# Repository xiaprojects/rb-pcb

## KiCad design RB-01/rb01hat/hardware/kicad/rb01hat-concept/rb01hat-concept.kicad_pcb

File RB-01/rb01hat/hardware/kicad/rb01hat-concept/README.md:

# RB01HAT Rev A concept board

**This is a visualisation, not the Rev A design. Do not fabricate it.** It shows what the plan in
[docs/06-custom-pcb.md](../../../docs/06-custom-pcb.md) could look like. The Rev 0 bring-up gate in
[hardware/kicad/README.md](../README.md) still applies, and `hardware/*.csv` stays the source of truth.

Everything here is generated. Change `generate.py`, not the KiCad files.

## What it is

- HAT+ outline, 65 x 56.5 mm, four layers: F.Cu signals, In1 GND, In2 3V3, B.Cu signals.
- Parts sit in zones Z1-Z6 of [docs/03-mechanical.md](../../../docs/03-mechanical.md).
- Nets and refdes come from [hardware/netlist.csv](../../netlist.csv). The script stops if any on-board row
  doesn't land on a pad of that net. U9-U12 and J12 are not here: they belong to the extension.
- Fully routed, and the KiCad DRC passes with 0 errors, 0 warnings and 0 unconnected items.
- Chip pinouts were read from the vendor datasheets (listed at `PIN_MAP` in `generate.py`).

A clean DRC proves the copper is consistent with the rules. It doesn't prove the circuit works.

## Renders

In `renders/`, 3840 x 2160 JPG: `-hero` and `-right` (3/4 views), `-top`, `-bottom`.

## Regenerate

```bash
python3 generate.py            # board, routing, DRC
python3 generate.py --preview  # plus 1600 x 900 renders
python3 generate.py --render   # plus 4K renders (several minutes)
```

It needs the system Python with KiCad 9's `pcbnew`, numpy and Pillow, plus a C compiler for `astar.c`. The
`kicad-packages3d` package is not installed here, so the first run downloads the 3D models it needs into
`3dmodels/`.

## Defaults for the open decisions

These are placeholders so a board could be drawn. They are not decisions.

| ID | Used here | Why |
|---|---|---|
| RA-1 IMU | ICM-20948 with 1.8 V LDO and I2C translator | The netlist part. Lifecycle status not checked. |
| RA-2 Outline | A: HAT+ outline, EGT bank off-board on J11 | Doc 06 recommendation |
| RA-3 TC connectors | 3.5 mm 2-pole terminal blocks, wires leaving over the top edge | Keeps leads off the board; other edges are taken by the extension and J2 |
| RA-4 Power | Pi 3V3, as in the netlist | Fewest added parts. Doc 06 prefers a local LDO. |
| RA-5 BME680 | On-board peninsula with milled slots and no copper pour | Doc 06 |
| RA-6 HAT+ ID pins | RB-EMS mapping unchanged (I2C0 on GPIO0/1) | Matches the netlist; keeps the HAT+ deviation |
| RA-7 Off-HAT signals | No connectors | Not in the netlist |

## Added parts (not in netlist.csv)

The DIY modules carry these on board; a chip-down board has to supply them.

| Refdes | Purpose |
|---|---|
| U15, R14-R16, C21 | PCA9306 between 3V3 I2C1 and the IMU's 1.8 V I/O, EN network, 1.8 V pull-ups |
| U16, C19, C20 | AP2112K-1.8 LDO for the IMU |
| C16-C18 | IMU VDD, VDDIO and REGOUT capacitors |
| J3-J6 | CHT1-CHT4 terminal blocks |
| C4-C15 | MAX31856 AVDD, DVDD and T+/T- capacitors |
| C22-C25, R17-R19 | BME680, ADS1115 and U14 decoupling, 5 V pull-ups, U14 EN network |
| R20-R23, C26-C29 | ADC input RC filters |

U13, R13 and TP1 are DNP on the DIY build but fitted here, because HAT+ needs the ID EEPROM.

## Not done

A real Rev A needs at least these:

- **A schematic and ERC.** There is no schematic: the board comes straight from the CSV and the tables in `generate.py`.
- **FFC access.** The HAT+ examples have a PCIe FFC cut-out in the left edge (y 20-37) and a display FFC slot.
  RB-01 uses both PCIe and DSI. This board has neither, and the BME680 peninsula sits in that left-edge band.
- **Second ADS1115 at 0x49.** rb-ems-go now reads `oilpressure` there, so A3 is out of date. See below.
- **Doc 06 circuitry left out:** 33 Ohm series resistors on SCLK and MOSI, clamps and the battery divider on the
  ADC inputs, ferrite-split supplies.
- **Thermocouple layout.** No isothermal copper islands, and T+/T- are not routed as tight pairs.
- **Layout review.** `generate.py` holds a simple maze router: no length or impedance control, and nobody has
  reviewed the routing, the return paths or the assembly.
- **Footprint checks.** `MS4525DO_DS_DIP-8` is drawn from the datasheet outline; confirm pads and drills against
  TE's current drawing. U1 uses a generic 3 x 3 mm QFN-24 with the exposed pad removed, because the ICM-20948 die
  pad must not be soldered; confirm it against the TDK land pattern.

## Known differences from the docs

- **Header position.** [docs/03-mechanical.md](../../../docs/03-mechanical.md) puts the 40-pin header at x = 29 from
  the board corner. The Pi 5 drawing and the HAT+ examples measure that 29 from the hole, so the centre is at
  x = 32.5 and pin 1 at x = 8.37. This board uses the drawing.
- **ADC channels.** Since rb-ems-go `55f0627` (2026-10-10), `ems-adc.json` reads A2-A3 as a differential pair and
  `oilpressure` at address 0x49. J2 and U8 follow `netlist.csv`, which still has oil pressure on A3.

## Render notes

- The MS4525DO 3D model is a simple one made by `generate.py` from the datasheet outline.
- U8 shows KiCad's MSOP-10 model, because the library has no VSSOP-10 model. The outline is the same.
- Straight-down views use side lights only, because a light on the vertical axis mirrors off the mask and turns it
  pink. Their cast shadows are off, through a throwaway `KICAD_CONFIG_HOME`; your own KiCad settings aren't touched.

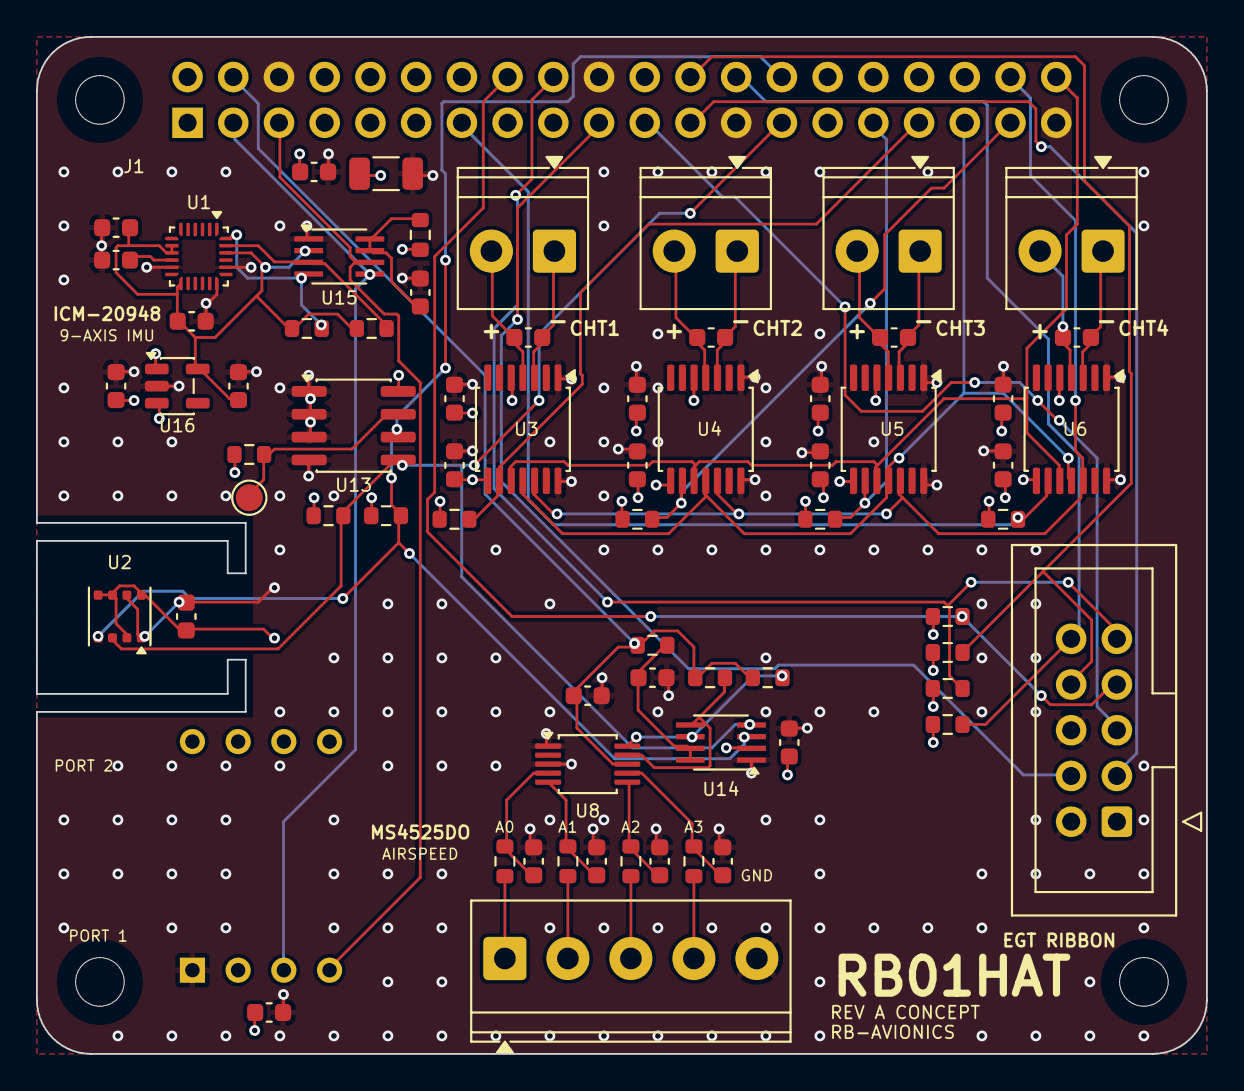
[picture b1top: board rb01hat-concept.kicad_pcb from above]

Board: 4 copper layers, 65.0 x 56.5 mm, 74 parts (1 on the bottom side), 46 nets.

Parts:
C1: 22u; C_1206_3216Metric
C2, C3, C4, C5, C6, C7, C8, C9, C10, C11, C12, C13, C14, C15, C16, C17, C18, C22, C23, C24, C26, C27, C28, C29: 100n; C_0603_1608Metric
C19, C20: 1u; C_0603_1608Metric
C21, C25: 100p; C_0603_1608Metric
H1, H2, H3, H4: M2.5; MountingHole_2.7mm_M2.5
J1: Pi 5 GPIO; PinSocket_2x20_P2.54mm_Vertical
J2: ADC IN; TerminalBlock_Phoenix_PT-1,5-5-3.5-H_1x05_P3.50mm_Horizontal
J3: CHT1; TerminalBlock_Phoenix_PT-1,5-2-3.5-H_1x02_P3.50mm_Horizontal
J4: CHT2; TerminalBlock_Phoenix_PT-1,5-2-3.5-H_1x02_P3.50mm_Horizontal
J5: CHT3; TerminalBlock_Phoenix_PT-1,5-2-3.5-H_1x02_P3.50mm_Horizontal
J6: CHT4; TerminalBlock_Phoenix_PT-1,5-2-3.5-H_1x02_P3.50mm_Horizontal
J11: EGT ribbon; IDC-Header_2x05_P2.54mm_Vertical
R1, R2, R3, R4, R5, R6, R7, R8, R17, R18: 10k; R_0603_1608Metric
R11, R12: 3k9; R_0603_1608Metric
R13, R20, R21, R22, R23: 1k; R_0603_1608Metric
R14, R19: 200k; R_0603_1608Metric
R15, R16: 2k2; R_0603_1608Metric
TP1: WP; TestPoint_Pad_D1.5mm
U1: ICM-20948; QFN-24-1EP_3x3mm_P0.4mm_EP1.75x1.6mm
U2: BME680; Bosch_LGA-8_3x3mm_P0.8mm_ClockwisePinNumbering
U3, U4, U5, U6: MAX31856; TSSOP-14_4.4x5mm_P0.65mm
U7: MS4525DO; MS4525DO_DS_DIP-8
U8: ADS1115; VSSOP-10_3x3mm_P0.5mm
U13: CAT24C32; SOIC-8_3.9x4.9mm_P1.27mm
U14, U15: PCA9306; SSOP-8_2.95x2.8mm_P0.65mm
U16: AP2112K-1.8; SOT-23-5

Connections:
1V8: C16.1, C17.1, C20.1, R15.1, R16.1, U1.8, U1.9, U1.13, U1.22, U15.2, U16.5
3V3: C1.1, C2.1, C3.1, C4.1, C5.1, C7.1, C8.1, C10.1, C11.1, C13.1, C14.1, C19.1, C22.1, C24.1, J1.1, J1.17, J11.1, R1.1, R2.1, R3.1, R4.1, R5.1, R6.1, R7.1, R8.1, R11.1, R12.1, R13.1, R14.1, U2.2, U2.5, U2.6, U2.8, U3.5, U3.8, U4.5, U4.8, U5.5, U5.8, U6.5, U6.8, U7.2, U13.8, U14.2, U16.1, U16.3
5V: C23.1, J1.4, R17.1, R18.1, R19.1, U8.8
ADC_A0: J2.1, R20.1
ADC_A0_F: C26.1, R20.2, U8.4
ADC_A1: J2.2, R21.1
ADC_A1_F: C27.1, R21.2, U8.5
ADC_A2: J2.3, R22.1
ADC_A2_F: C28.1, R22.2, U8.6
ADC_A3: J2.4, R23.1
ADC_A3_F: C29.1, R23.2, U8.7
CHT1_CS_N: J1.33, R1.2, U3.9
CHT1_TN: C6.2, J3.1, U3.3
CHT1_TP: C6.1, J3.2, U3.4
CHT2_CS_N: J1.37, R2.2, U4.9
CHT2_TN: C9.2, J4.1, U4.3
CHT2_TP: C9.1, J4.2, U4.4
CHT3_CS_N: J1.31, R3.2, U5.9
CHT3_TN: C12.2, J5.1, U5.3
CHT3_TP: C12.1, J5.2, U5.4
CHT4_CS_N: J1.13, R4.2, U6.9
CHT4_TN: C15.2, J6.1, U6.3
CHT4_TP: C15.1, J6.2, U6.4
EEPROM_WP: R13.2, TP1.1, U13.7
EGT1_CS_N: J1.16, J11.7, R5.2
EGT2_CS_N: J1.24, J11.8, R6.2
EGT3_CS_N: J1.18, J11.9, R7.2
EGT4_CS_N: J1.26, J11.10, R8.2
GND: C1.2, C2.2, C3.2, C4.2, C5.2, C7.2, C8.2, C10.2, C11.2, C13.2, C14.2, C16.2, C17.2, C18.2, C19.2, C20.2, C21.2, C22.2, C23.2, C24.2, C25.2, C26.2, C27.2, C28.2, C29.2, J1.6, J1.20, J1.25, J1.39, J2.5, J11.2, J11.6, U1.11, U1.18, U1.20, U2.1, U2.7, U3.1, U3.14, U4.1, U4.14, U5.1, U5.14, U6.1, U6.14, U7.1, U8.1, U8.3, U13.1, U13.2, U13.3, U13.4, U14.1, U15.1, U16.2
I2C0_EN: C25.1, R19.2, U14.7, U14.8
I2C0_SCL: J1.28, R12.2, U2.4, U13.6, U14.3
I2C0_SCL_5V: R18.2, U8.10, U14.6
I2C0_SDA: J1.27, R11.2, U2.3, U13.5, U14.4
I2C0_SDA_5V: R17.2, U8.9, U14.5
I2C1_EN: C21.1, R14.2, U15.7, U15.8
I2C1_SCL: J1.5, U7.4, U15.6
I2C1_SCL_1V8: R16.2, U1.23, U15.3
I2C1_SDA: J1.3, U7.3, U15.5
I2C1_SDA_1V8: R15.2, U1.24, U15.4
IMU_REGOUT: C18.1, U1.10
SPI0_MISO: J1.21, J11.5
SPI0_MOSI: J1.19, J11.4
SPI0_SCLK: J1.23, J11.3
SPI1_MISO: J1.35, U3.11, U4.11, U5.11, U6.11
SPI1_MOSI: J1.38, U3.12, U4.12, U5.12, U6.12
SPI1_SCLK: J1.40, U3.10, U4.10, U5.10, U6.10
